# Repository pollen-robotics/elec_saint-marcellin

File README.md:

# "elec_saint-marcellin" Electronic Board

"elec_saint-marcellin" is a USB 2.0 hub with USB type C connectors and a Dynamixel converter.

## Releases
| Release | Date       | Designer | Check  | Comments                               |
|---------|------------|----------|--------|----------------------------------------|
| A1      | 26/06/2025 | EB       | SN     | Initial drawing                        |
| B1      | 23/11/2026 | EB       | SN     |[fixed] Dynamixel-X connectors were 180 deg |

## Basically
 - Designed with KiCAD 10.

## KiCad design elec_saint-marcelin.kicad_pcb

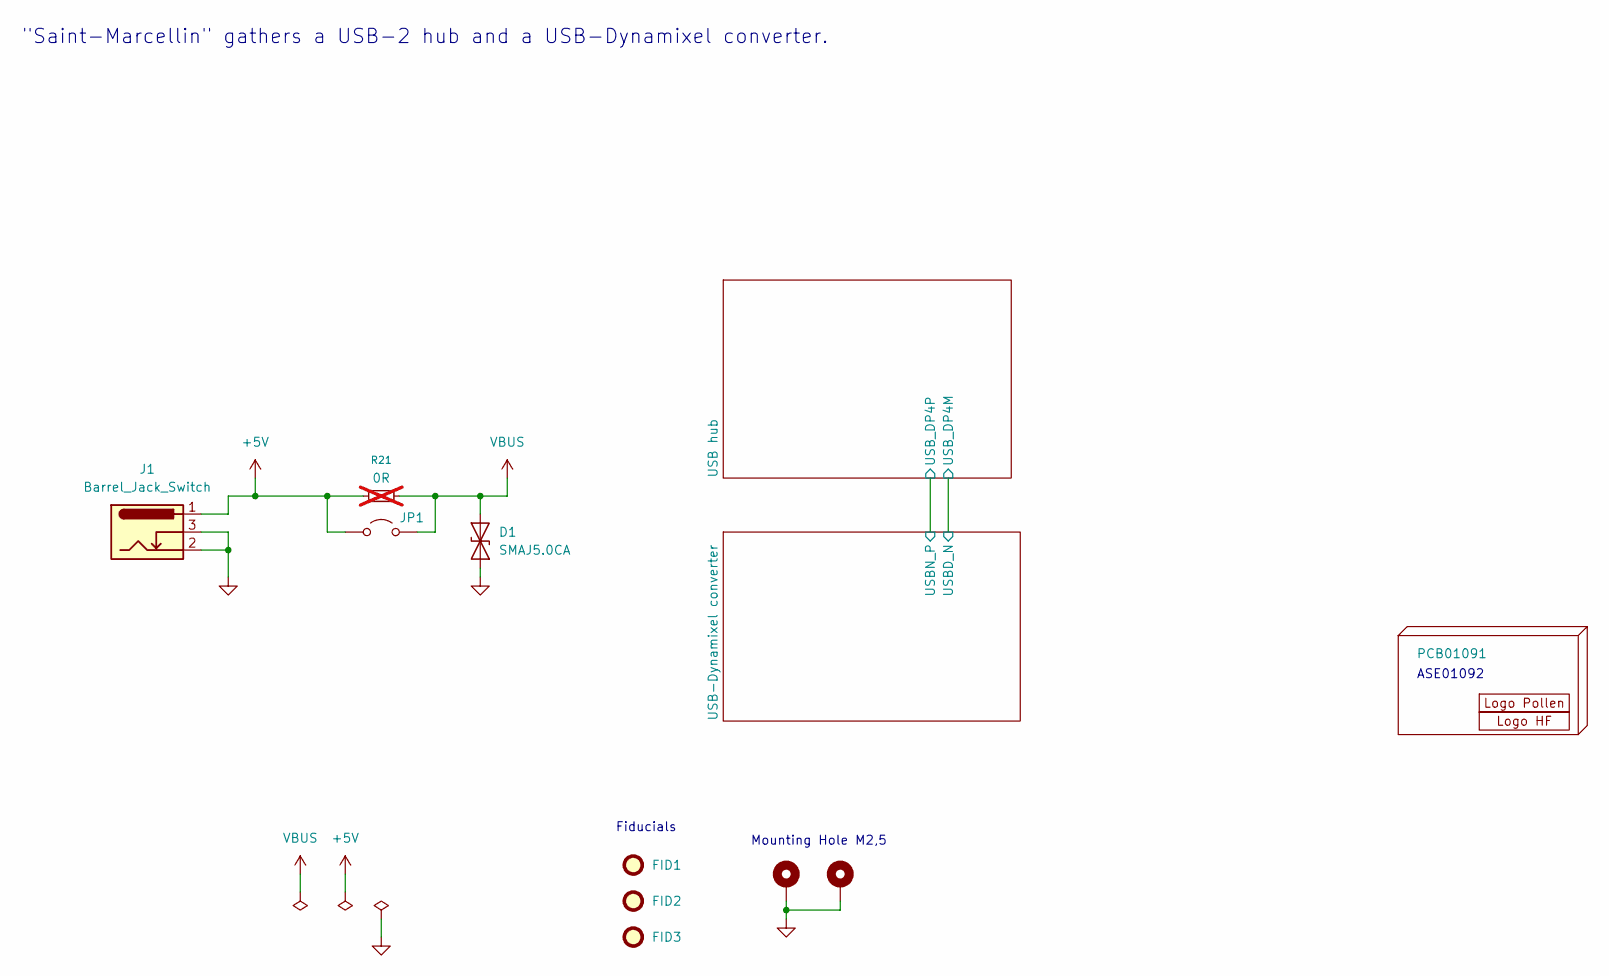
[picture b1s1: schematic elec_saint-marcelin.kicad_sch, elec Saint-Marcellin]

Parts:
D1: SMAJ5.0CA; D_SMA; LCSC C83324
FID1, FID2, FID3: DNP Fiducial; Fiducial_1mm_Mask2mm
H1: PCB01091
H2: DNP Logo Pollen 2021; Logo_Pollen_2021_hex_only
H3, H4: MountingHole_Pad; MountingHole_2.7mm_M2.5_DIN965_Pad_TopBottom
H7: Logo HF 2025; Logo_HF_2025
J1: Barrel_Jack_Switch; Shou_Han_DC005; LCSC C431533
JP1: Jumper_2_Open; SolderJumper-2_P1.3mm_Open_RoundedPad1.0x1.5mm
R21: 0R; R_0603_1608Metric; not fitted

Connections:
+5V: J1.1, JP1.1 (A), R21.1; also elsewhere on the board
GND: D1.1 (A1), H3.1 (1_1), H4.1 (1_1), J1.2, J1.3; also elsewhere on the board
VBUS: D1.2 (A2), JP1.2 (B), R21.2; also elsewhere on the board

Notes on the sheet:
Mounting Hole M2,5
Fiducials
ASE01092
"Saint-Marcellin" gathers a USB-2 hub and a USB-Dynamixel converter.

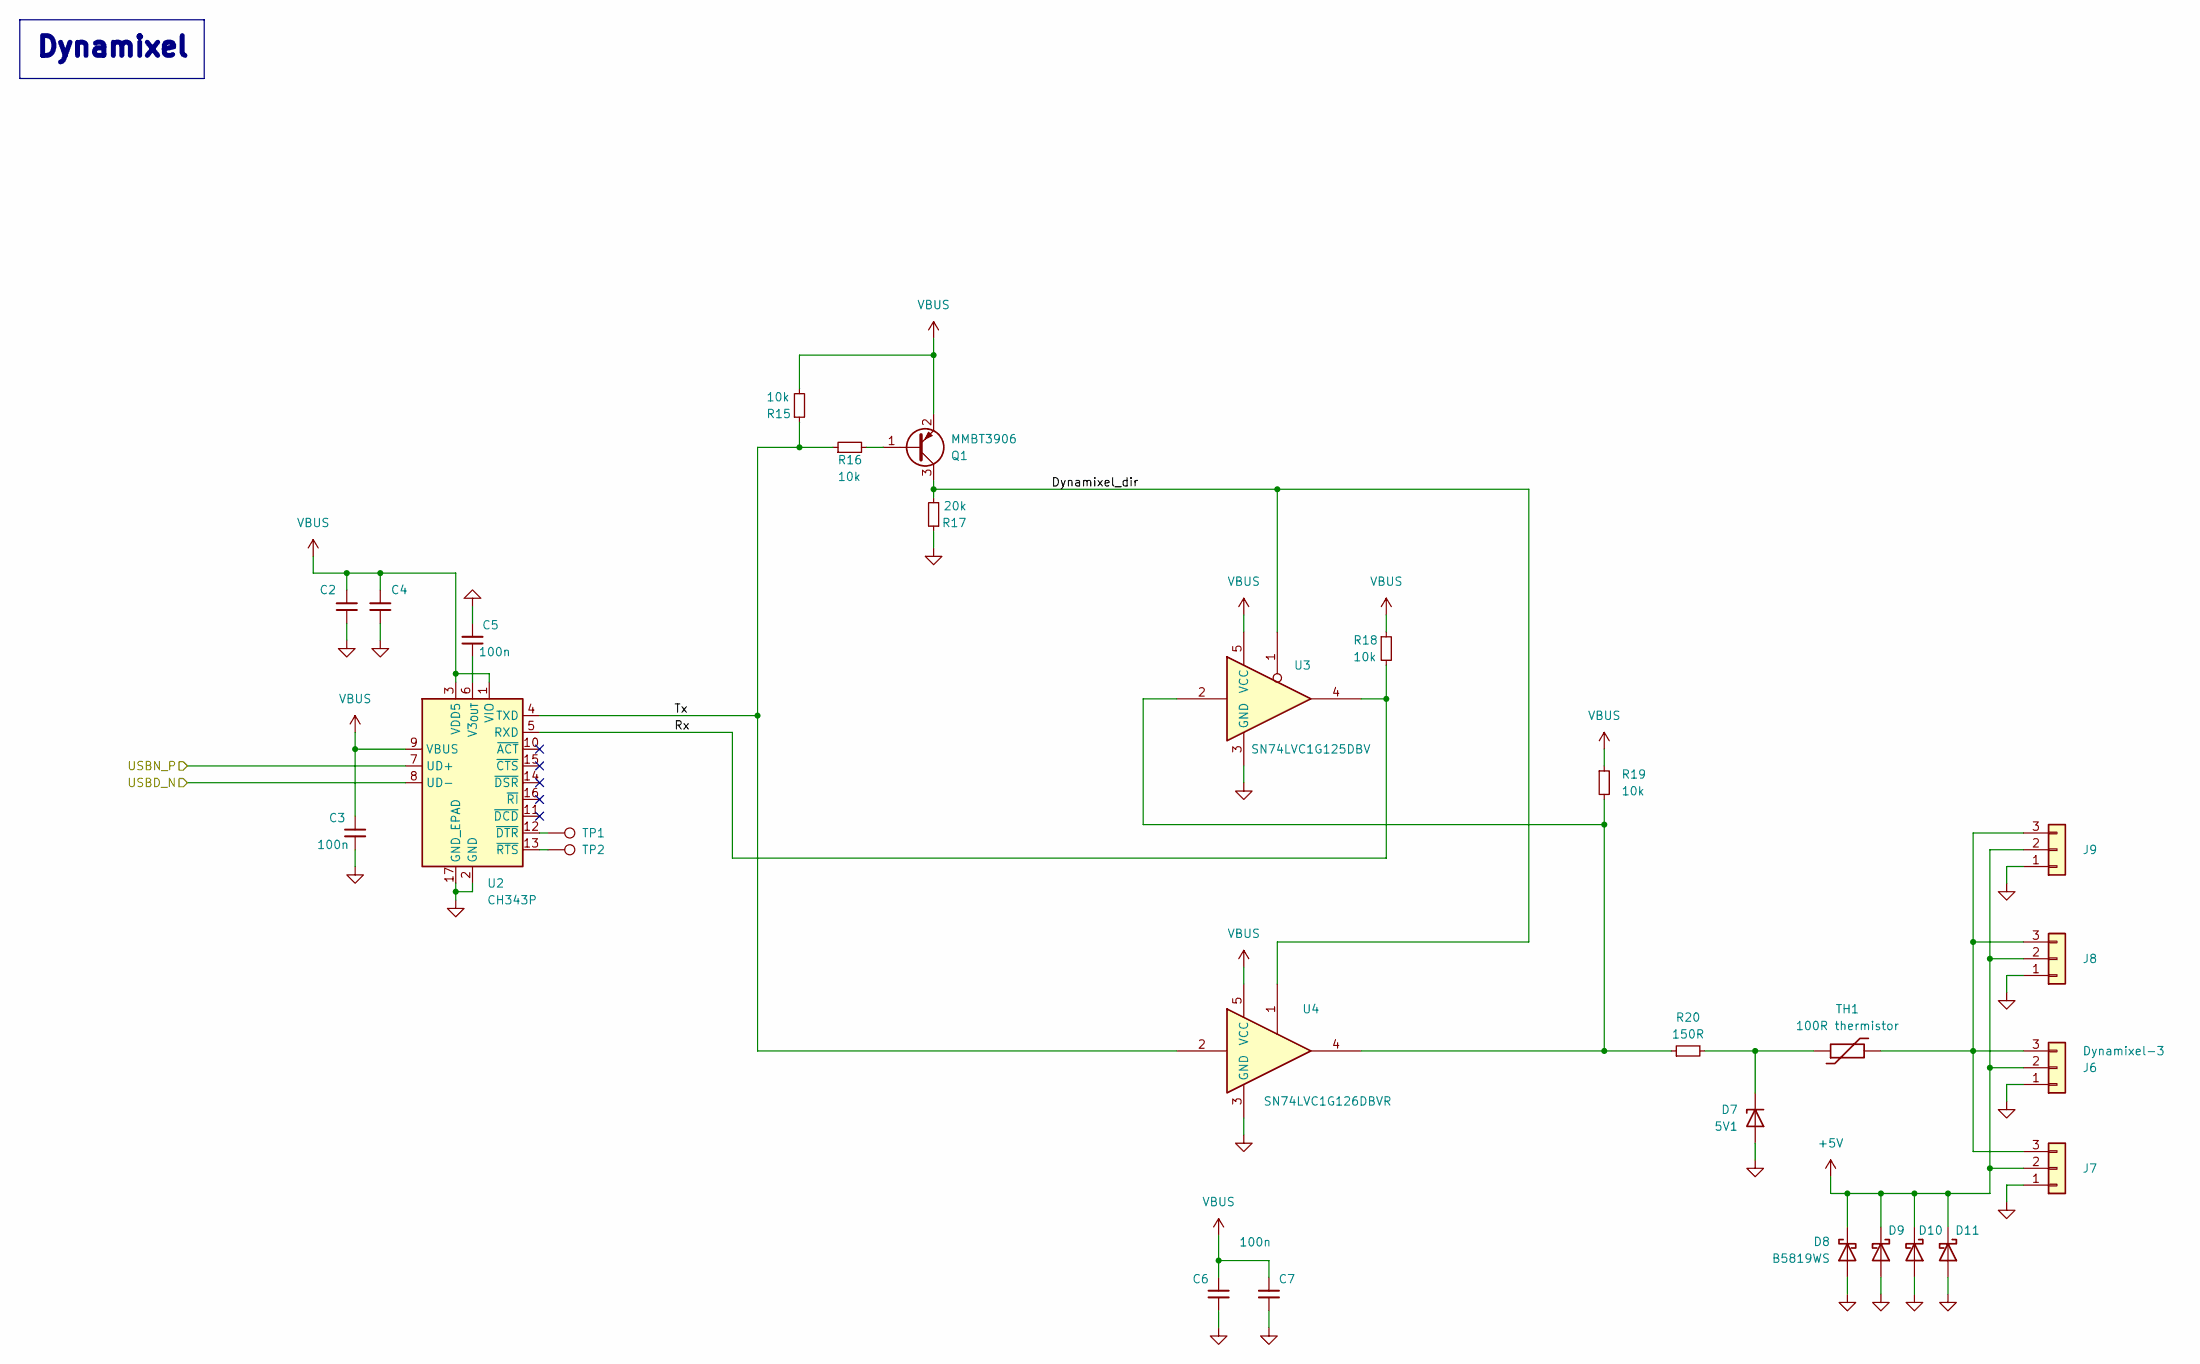
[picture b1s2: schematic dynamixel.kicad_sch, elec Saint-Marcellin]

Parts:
C2, C4: 1uF-6V3; C_0603_1608Metric; LCSC C15849
C3, C5, C6, C7: 100n; C_0603_1608Metric; LCSC C85864
D7: 5V1; D_SOD-323; LCSC C151348
D8, D9, D10, D11: B5819WS; D_SOD-323; LCSC C78734
J6, J7, J8, J9: Dynamixel-3; JST_EH_B3B-EH-A_1x03_P2.50mm_Vertical; LCSC C160259
Q1: MMBT3906; SOT-23; LCSC C727128
R15, R16, R18, R19: 10k; R_0402_1005Metric; LCSC C25744
R17: 20k; R_0402_1005Metric; LCSC C2906867
R20: 150R; R_0402_1005Metric; LCSC C138054
TH1: 100R thermistor; R_0603_1608Metric; LCSC C913703
TP1, TP2: TestPoint; TestPoint_Pad_D1.0mm
U2: CH343P; WCH_QFN-16-1EP_3x3mm_P0.5mm_EP1.8x1.8mm; LCSC C2846043
U3: SN74LVC1G125DBV; SOT-23-5; LCSC C23654
U4: SN74LVC1G126DBVR; SOT-23-5; LCSC C7834

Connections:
+5V: D8.1 (K), D9.1 (K), D10.1 (K), D11.1 (K), J6.2, J7.2, J8.2, J9.2; also elsewhere on the board
/USB hub/USB_DP4M: U2.8 (UD-); also elsewhere on the board
/USB hub/USB_DP4P: U2.7 (UD+); also elsewhere on the board
/USB-Dynamixel converter/Dynamixel_dir: Q1.3 (C), R17.2, U3.1, U4.1
/USB-Dynamixel converter/Rx: R18.2, U2.5 (RXD), U3.4
/USB-Dynamixel converter/Tx: R15.1, R16.1, U2.4 (TXD), U4.2
GND: C2.1, C3.1, C4.1, C5.2, C6.1, C7.1, D7.2 (A), D8.2 (A), D9.2 (A), D10.2 (A), D11.2 (A), J6.1, J7.1, J8.1, J9.1, R17.1, U2.2 (GND), U2.17 (GND_EPAD), U3.3 (GND), U4.3 (GND); also elsewhere on the board
unnamed: D7.1 (K), R20.2, TH1.1
unnamed: J6.3, J7.3, J8.3, J9.3, TH1.2
unnamed: Q1.1 (B), R16.2
unnamed: R19.2, R20.1, U3.2, U4.4
unnamed: C5.1, U2.6 (V3_{OUT})
unnamed: TP1.1 (1_1), U2.12 (~DTR)
unnamed: TP2.1 (1_1), U2.13 (~RTS)
VBUS: C2.2, C3.2, C4.2, C6.2, C7.2, Q1.2 (E), R15.2, R18.1, R19.1, U2.1 (VIO), U2.3 (VDD5), U2.9 (VBUS), U3.5 (VCC), U4.5 (VCC); also elsewhere on the board

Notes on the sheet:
Dynamixel

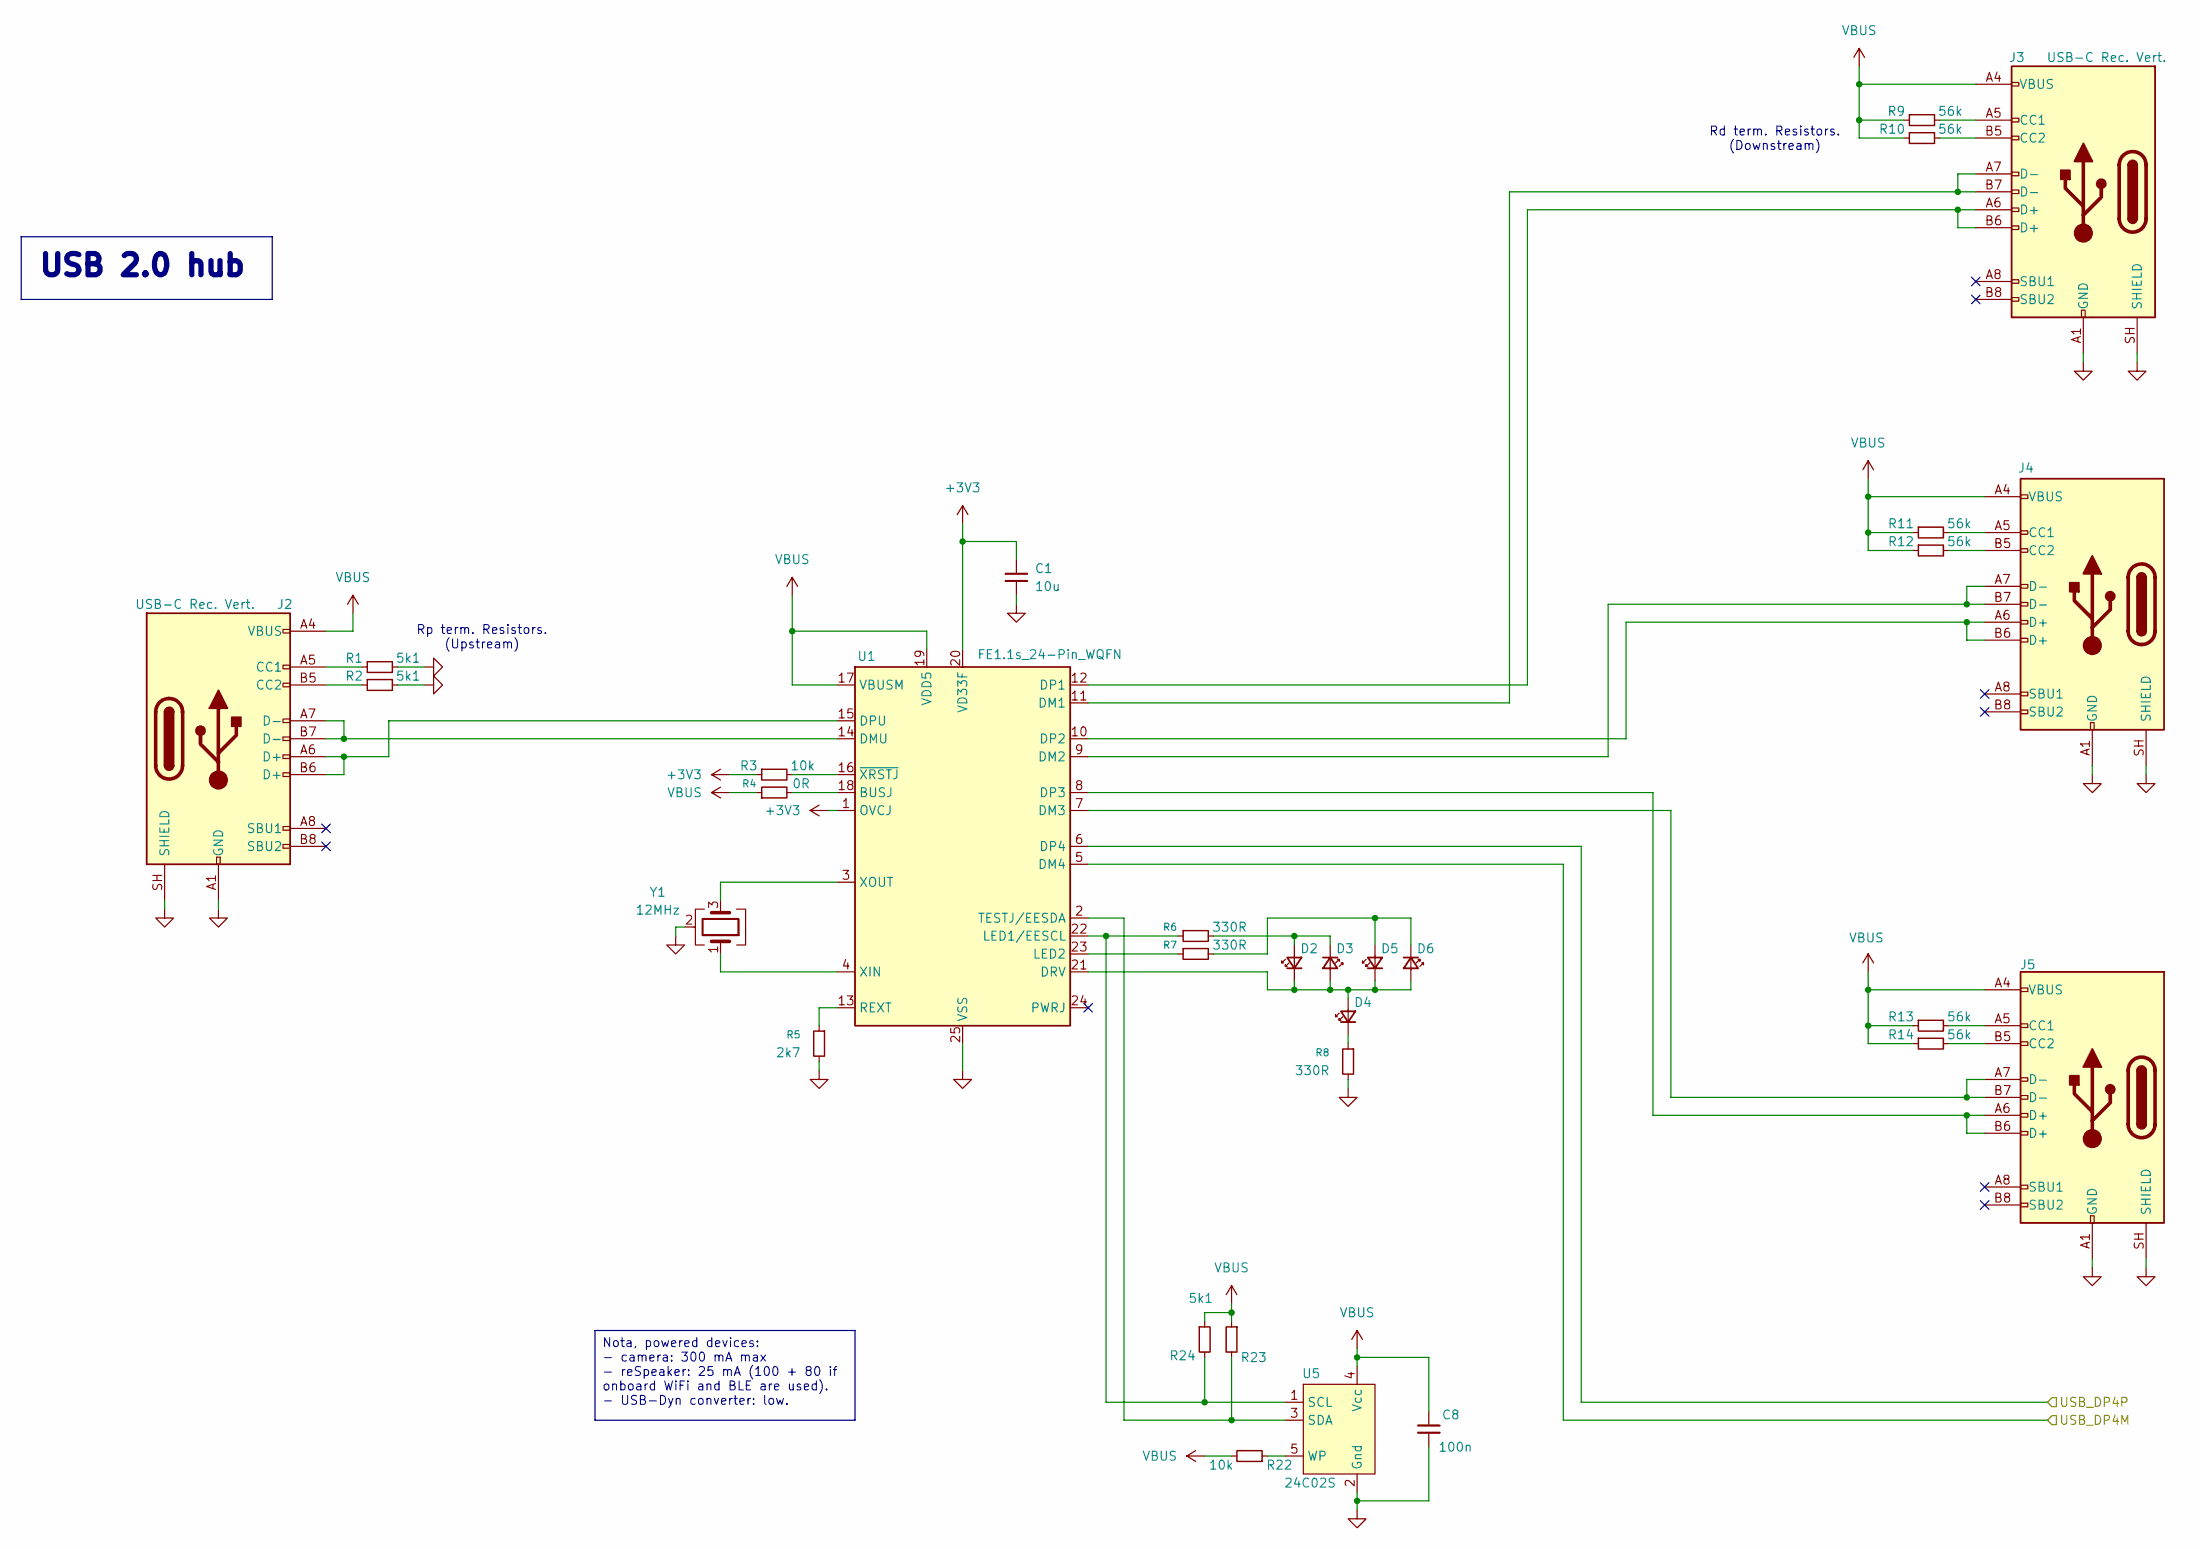
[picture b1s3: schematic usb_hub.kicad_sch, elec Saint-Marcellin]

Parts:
C1: 10u; C_0603_1608Metric; LCSC C1691
C8: 100n; C_0603_1608Metric; LCSC C85864
D2, D5: LED_Small; LED_0603_1608Metric; LCSC C19171301
D3, D6: LED_Small; LED_0603_1608Metric; LCSC C84263
D4: LED_Small; LED_0603_1608Metric; LCSC C7429915
J2: USB-C Rec. Vert.; USB-C-SMD_TYPE-C-6PIN-2MD-073 Shou Han - C2765186; LCSC C2765186
J3, J4, J5: USB-C Rec. Vert.; USB-C_16p_vert_Shou-Han_TYPE-C 16P LTH6.8 - C5187468; LCSC C5187468
R1, R2, R23, R24: 5k1; R_0402_1005Metric; LCSC C25905
R3, R22: 10k; R_0402_1005Metric; LCSC C25744
R4: 0R; R_0402_1005Metric; LCSC C106231
R5: 2k7; R_0402_1005Metric; LCSC C138017
R6, R7, R8: 330R; R_0402_1005Metric; LCSC C105875
R9, R10, R11, R12, R13, R14: 56k; R_0402_1005Metric; LCSC C114756
U1: FE1.1s_24-Pin_WQFN; WQFN-24-1EP_4x4mm_P0.5mm_EP2.6x2.6mm; LCSC C6776948
U5: 24C02S; SOT-23-5; LCSC C18723540
Y1: 12MHz; Crystal_SMD_3225-4Pin_3.2x2.5mm; LCSC C133334

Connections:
+3V3: C1.1, R3.1, U1.1 (OVCJ), U1.20 (VD33F)
/USB hub/USB_DP4M: U1.5 (DM4); also elsewhere on the board
/USB hub/USB_DP4P: U1.6 (DP4); also elsewhere on the board
GND: C1.2, C8.1, J2.A1 (GND), J2.A12 (GND), J2.B1 (GND), J2.B12 (GND), J2.SH (SHIELD), J3.A1 (GND), J3.A12 (GND), J3.B1 (GND), J3.B12 (GND), J3.SH (SHIELD), J4.A1 (GND), J4.A12 (GND), J4.B1 (GND), J4.B12 (GND), J4.SH (SHIELD), J5.A1 (GND), J5.A12 (GND), J5.B1 (GND), J5.B12 (GND), J5.SH (SHIELD), R1.2, R2.2, R5.2, R8.2, U1.25 (VSS), U5.2 (Gnd), Y1.2 (G), Y1.4 (G); also elsewhere on the board
unnamed: D2.2 (A), D3.1 (K), R6.2
unnamed: D2.1 (K), D3.2 (A), D4.2 (A), D5.1 (K), D6.2 (A), U1.21 (DRV)
unnamed: D4.1 (K), R8.1
unnamed: D5.2 (A), D6.1 (K), R7.2
unnamed: J2.A5 (CC1), R1.1
unnamed: J2.B5 (CC2), R2.1
unnamed: J3.A5 (CC1), R9.2
unnamed: J3.B5 (CC2), R10.2
unnamed: J4.A5 (CC1), R11.2
unnamed: J4.B5 (CC2), R12.2
unnamed: J5.A5 (CC1), R13.2
unnamed: J5.B5 (CC2), R14.2
unnamed: R4.2, U1.18 (BUSJ)
unnamed: J3.A7 (D-), J3.B7 (D-), U1.11 (DM1)
unnamed: J4.A7 (D-), J4.B7 (D-), U1.9 (DM2)
unnamed: J5.A7 (D-), J5.B7 (D-), U1.7 (DM3)
unnamed: J2.A7 (D-), J2.B7 (D-), U1.14 (DMU)
unnamed: J3.A6 (D+), J3.B6 (D+), U1.12 (DP1)
unnamed: J4.A6 (D+), J4.B6 (D+), U1.10 (DP2)
unnamed: J5.A6 (D+), J5.B6 (D+), U1.8 (DP3)
unnamed: J2.A6 (D+), J2.B6 (D+), U1.15 (DPU)
unnamed: R6.1, R24.2, U1.22 (LED1/EESCL), U5.1 (SCL)
unnamed: R7.1, U1.23 (LED2)
unnamed: R5.1, U1.13 (REXT)
unnamed: R23.2, U1.2 (TESTJ/EESDA), U5.3 (SDA)
unnamed: U1.4 (XIN), Y1.1
unnamed: U1.3 (XOUT), Y1.3
unnamed: R3.2, U1.16 (~XRSTJ)
unnamed: R22.1, U5.5 (WP)
VBUS: C8.2, J2.A4 (VBUS), J2.A9 (VBUS), J2.B4 (VBUS), J2.B9 (VBUS), J3.A4 (VBUS), J3.A9 (VBUS), J3.B4 (VBUS), J3.B9 (VBUS), J4.A4 (VBUS), J4.A9 (VBUS), J4.B4 (VBUS), J4.B9 (VBUS), J5.A4 (VBUS), J5.A9 (VBUS), J5.B4 (VBUS), J5.B9 (VBUS), R4.1, R9.1, R10.1, R11.1, R12.1, R13.1, R14.1, R22.2, R23.1, R24.1, U1.17 (VBUSM), U1.19 (VDD5), U5.4 (Vcc); also elsewhere on the board

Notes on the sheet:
Rd term. Resistors. (Downstream)
Rp term. Resistors. (Upstream)
Nota, powered devices: - camera: 300 mA max - reSpeaker: 25 mA (100 + 80 if onboard WiFi and BLE are used). - USB-Dyn converter: low.
USB 2.0 hub

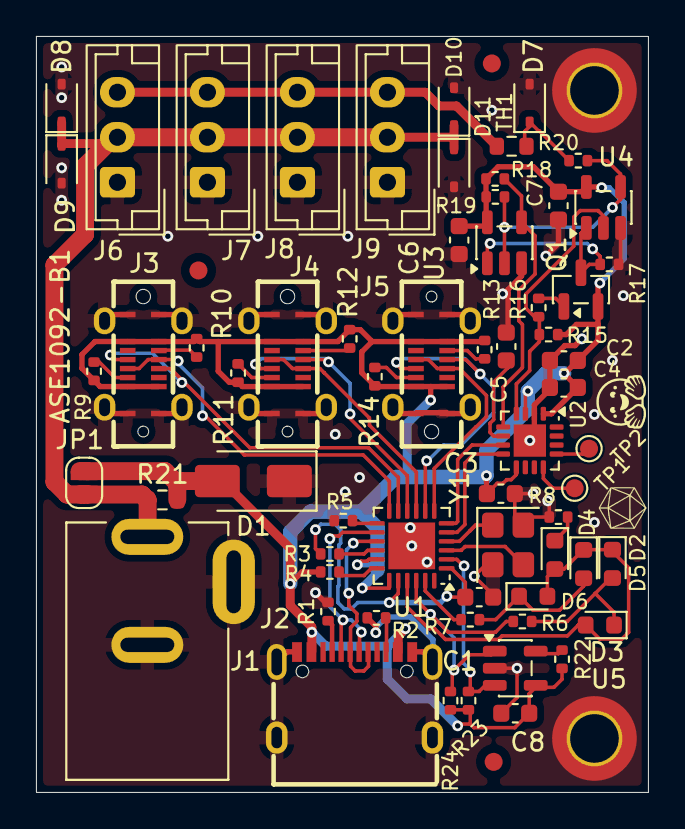
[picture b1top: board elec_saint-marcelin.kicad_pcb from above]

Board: 2 copper layers, 34.0 x 42.0 mm, 70 parts (0 on the bottom side), 45 nets.

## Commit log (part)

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2025-06-26 [init] Ready to be produced by JLCPCB
2025-06-26 [fixed] D2/5 orientation.
2025-06-26 [fixed] review by Stevo, Vbus/5V rearranged, EEPROM for USB id added.
2025-06-26 [added] EEPROM datasheet + 3d models of the hub part.
2025-07-04 [update] few corrections after getting the board from JLC (that seems to operate as expected).
2025-10-06 [added] Finaly not used in Reachy min Finaly not used in Reachy minii
